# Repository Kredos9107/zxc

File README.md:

1
2
3
4
5
6
изменяю файл в ветке 2 для последующего слияния

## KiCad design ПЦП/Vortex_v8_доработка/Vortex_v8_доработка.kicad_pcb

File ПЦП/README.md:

# ПЦП — «Водяной вихрь»

- `Vortex_v8_доработка/` — актуальная плата KiCad, схема, посадочные места и результаты проверки. Открывать `Vortex_v8_доработка.kicad_pro`.
- `led_test.ino` — сохранённая прошивка управления насосом и подсветкой.
- `encoder_test/` — тест энкодера.
- `encoder_test_backup/` — резервная копия прошивки ESP32 до теста энкодера; нужна для восстановления.
- `состояние.md`, `корпус.md` — описание проекта и корпуса. Состояние записано 28.10.2026; сведения о плате v8 от 01.11.2026 находятся в её `ПРОЧИТАЙ.txt`.
- `PROJECT-CONTEXT.md`, `AGENTS.md`, `instructions-original.txt` — контекст и инструкции.
- `Старые_версии_и_разработка.zip` — версии платы v2–v7, пробные разводки, исходные скрипты, промежуточные платы v8 и служебные данные экспорта. Для запуска старых скриптов распаковать архив в отдельную папку с сохранением структуры.

При уборке 02.11.2026 старые наработки перенесены в архив с проверкой контрольных сумм. Точные копии материалов из `materials/` удалены; основные экземпляры находятся в корне.
Плата v8 исправлена и проверена 02.11.2026. Текущие результаты и аппаратные ограничения: `Vortex_v8_доработка/Проверка_логики.txt`. Предыдущие файлы сохранены в существующем ZIP, раздел `до_проверки_v8_2026-11-02/`. Прошивка led_test.ino остаётся для старой распиновки.

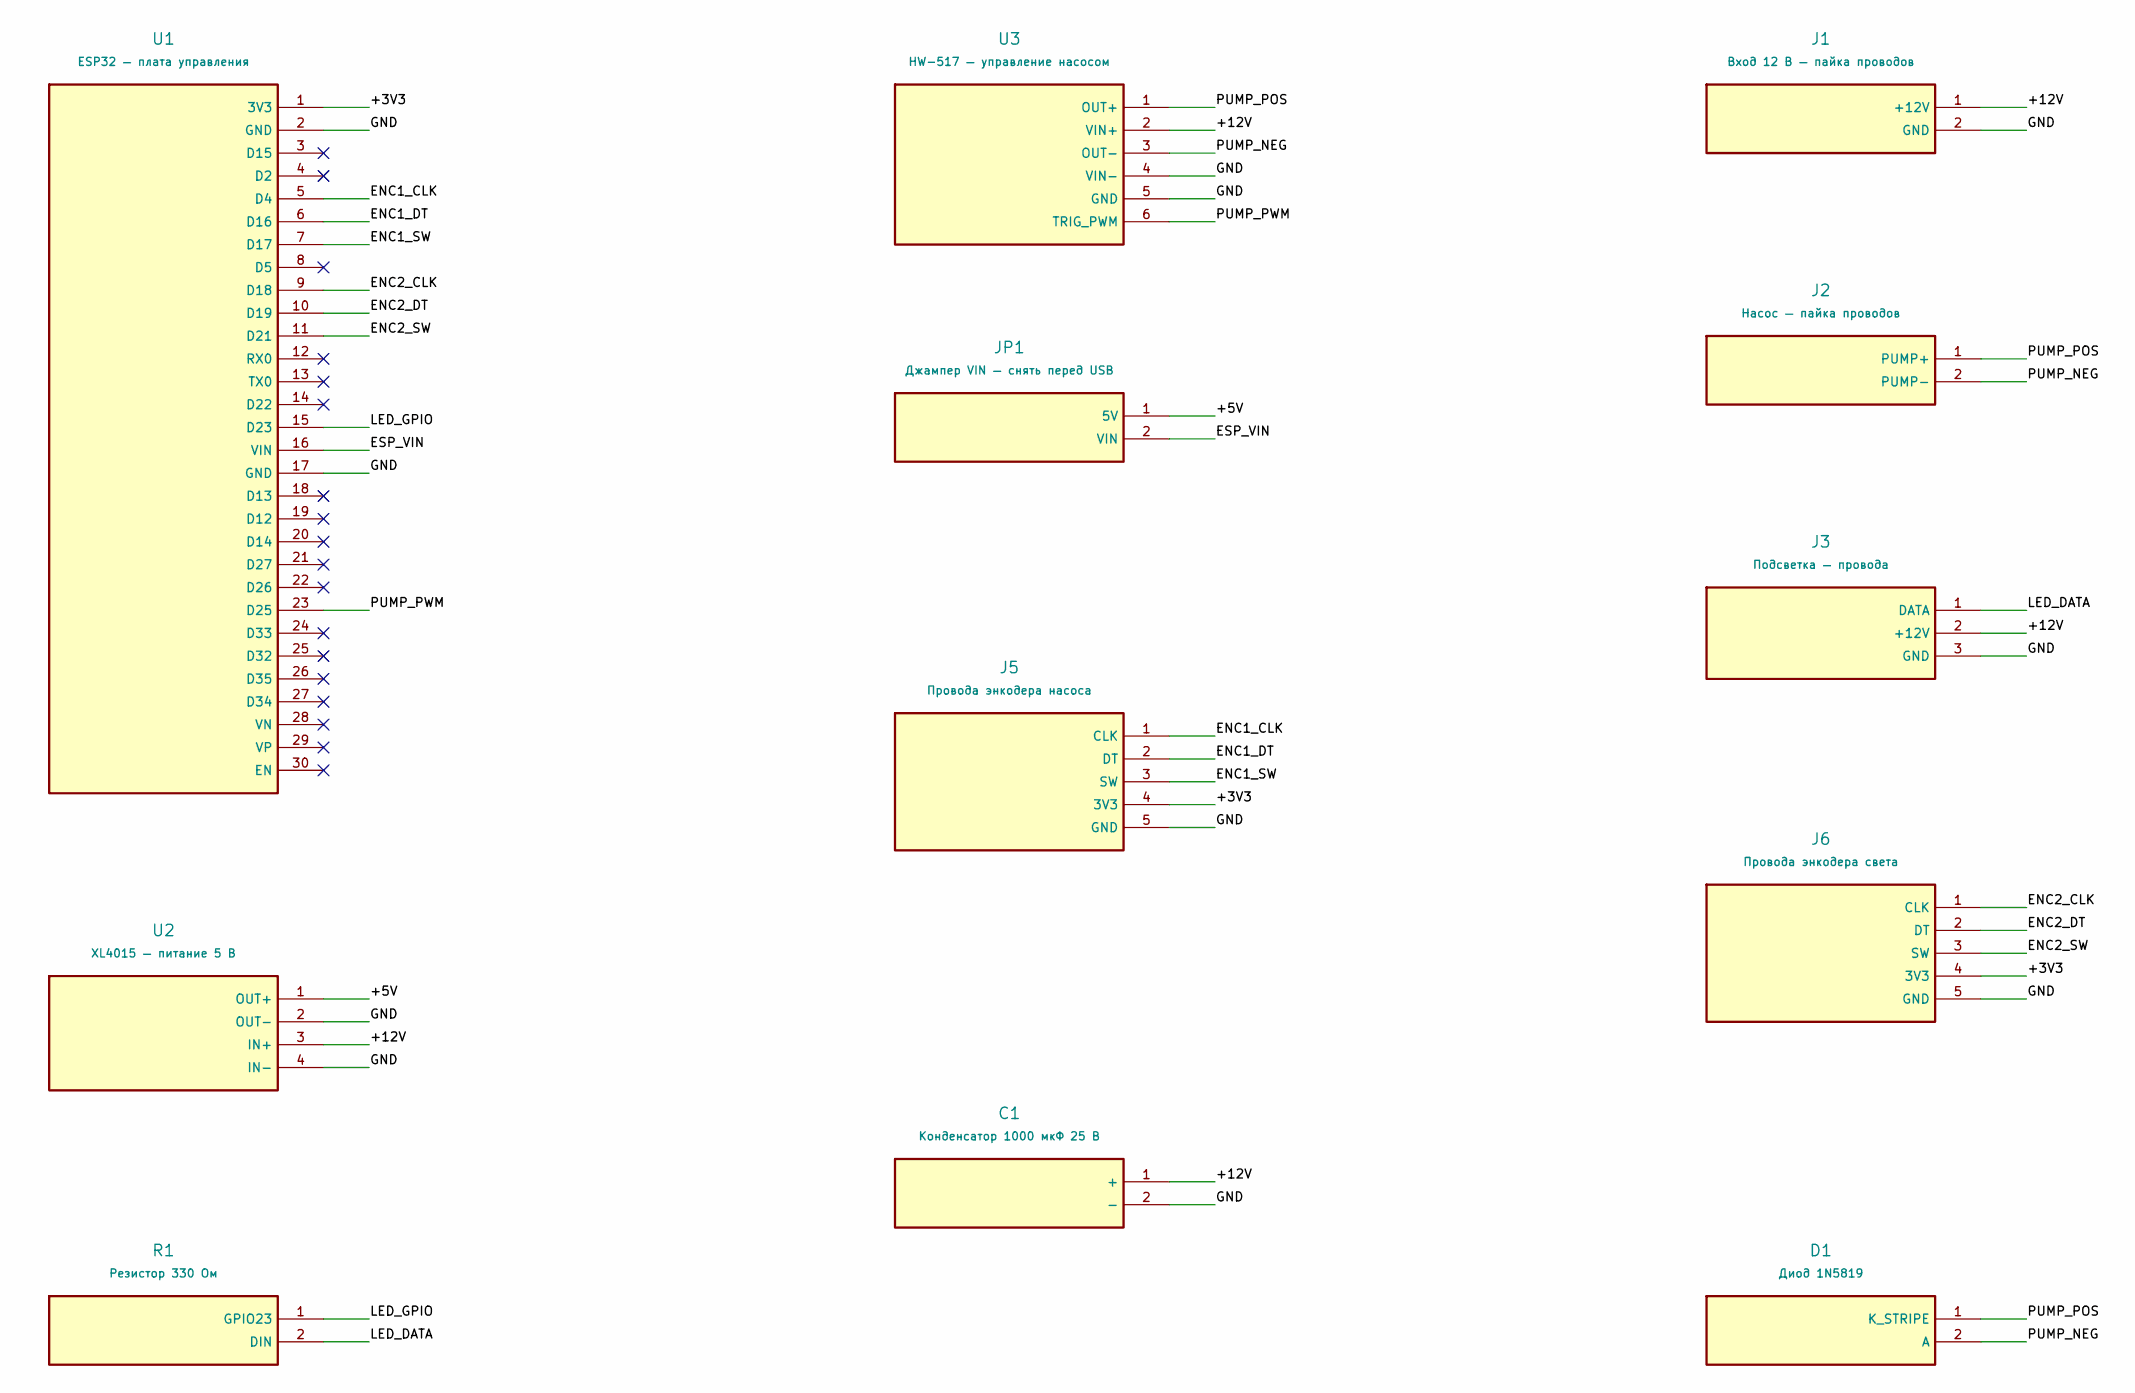
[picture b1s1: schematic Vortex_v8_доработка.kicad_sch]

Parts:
C1: Конденсатор 1000 мкФ 25 В; 1000uF_25V
D1: Диод 1N5819; 1N5819
J1: Вход 12 В — пайка проводов; 12V_INPUT_SOLDER
J2: Насос — пайка проводов; PUMP_SOLDER
J3: Подсветка — провода; WS2811_SOLDER
J5: Провода энкодера насоса; ENC1_HEADER_V7
J6: Провода энкодера света; ENC2_HEADER_V7
JP1: Джампер VIN — снять перед USB; VIN_POWER_JUMPER
R1: Резистор 330 Ом; 330R
U1: ESP32 — плата управления; ESP32_30P_SOCKET_PRELIM
U2: XL4015 — питание 5 В; XL4015_SOCKET_20x50_PRELIM
U3: HW-517 — управление насосом; HW517_FULL_SOCKET_PRELIM

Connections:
/+3V3: J5.4 (3V3), J6.4 (3V3), U1.1 (3V3)
/+5V: JP1.1 (5V), U2.1 (OUT+)
/+12V: C1.1 (+), J1.1 (+12V), J3.2 (+12V), U2.3 (IN+), U3.2 (VIN+)
/ENC1_CLK: J5.1 (CLK), U1.5 (D4)
/ENC1_DT: J5.2 (DT), U1.6 (D16)
/ENC1_SW: J5.3 (SW), U1.7 (D17)
/ENC2_CLK: J6.1 (CLK), U1.9 (D18)
/ENC2_DT: J6.2 (DT), U1.10 (D19)
/ENC2_SW: J6.3 (SW), U1.11 (D21)
/ESP_VIN: JP1.2 (VIN), U1.16 (VIN)
/GND: C1.2 (-), J1.2 (GND), J3.3 (GND), J5.5 (GND), J6.5 (GND), U1.2 (GND), U1.17 (GND), U2.2 (OUT-), U2.4 (IN-), U3.4 (VIN-), U3.5 (GND)
/LED_DATA: J3.1 (DATA), R1.2 (DIN)
/LED_GPIO: R1.1 (GPIO23), U1.15 (D23)
/PUMP_NEG: D1.2 (A), J2.2 (PUMP-), U3.3 (OUT-)
/PUMP_POS: D1.1 (K_STRIPE), J2.1 (PUMP+), U3.1 (OUT+)
/PUMP_PWM: U1.23 (D25), U3.6 (TRIG_PWM)

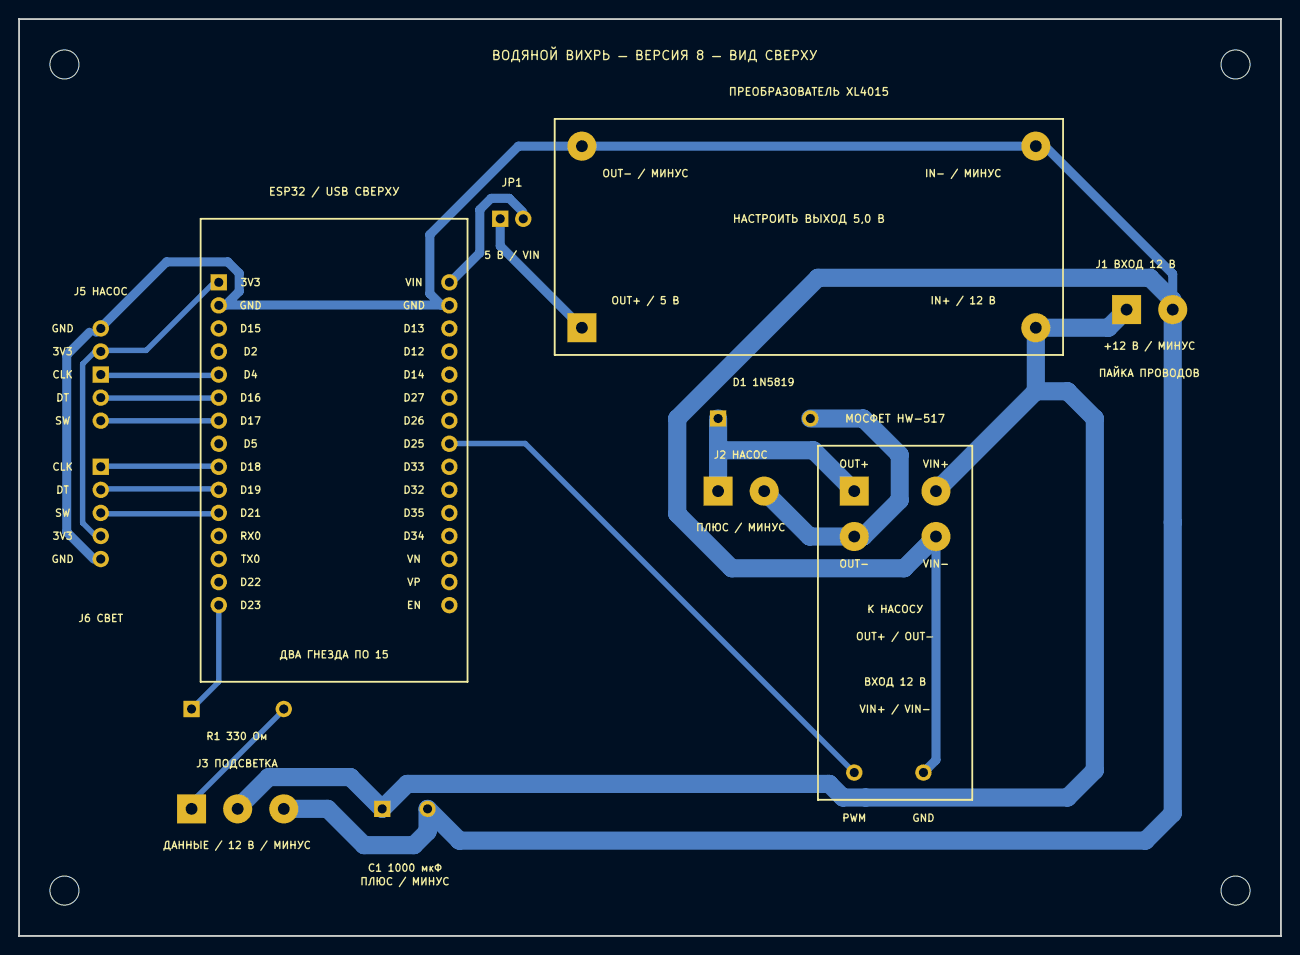
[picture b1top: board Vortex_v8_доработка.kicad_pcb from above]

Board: 2 copper layers, 139.0 x 101.0 mm, 16 parts (0 on the bottom side), 16 nets.

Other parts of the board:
H1, H2, H3, H4: (no value)

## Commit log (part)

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2026-02-03 добавляю текстовый файл с ноута (тест)
2026-02-03 изменение во 2 ветке
2026-02-09 мигать
2026-02-09 switch
2026-02-09 auto
2026-02-17 ЦАП финиш
2026-02-21 лаба 226
2026-02-21 226 done
2026-02-22 251 start
2026-02-22 52 ''
2026-02-23 251 finally
2026-03-02 adc2
2026-03-16 Create 67
2026-04-03 251f
